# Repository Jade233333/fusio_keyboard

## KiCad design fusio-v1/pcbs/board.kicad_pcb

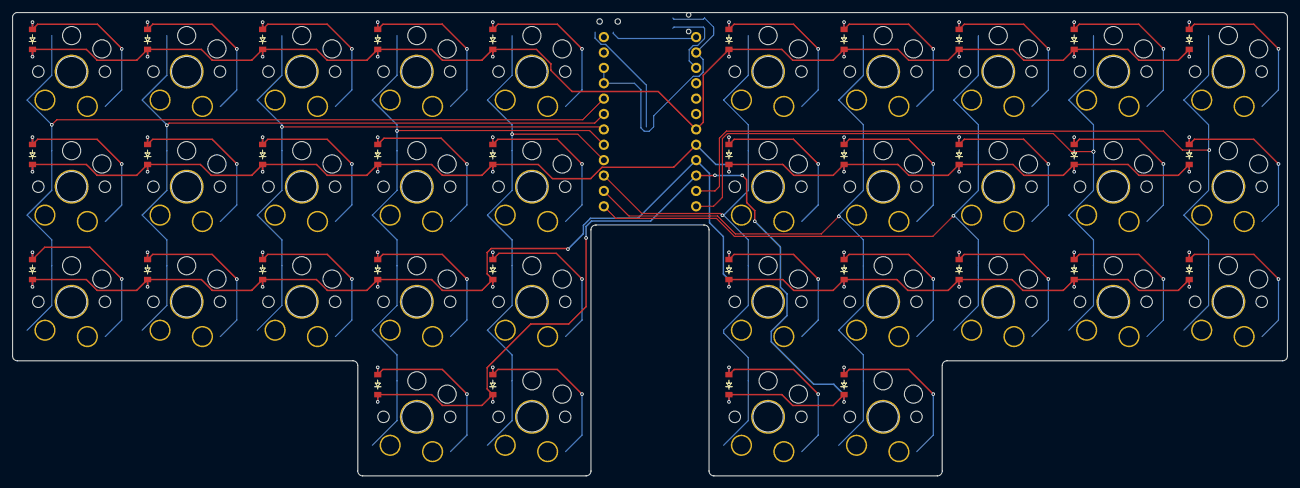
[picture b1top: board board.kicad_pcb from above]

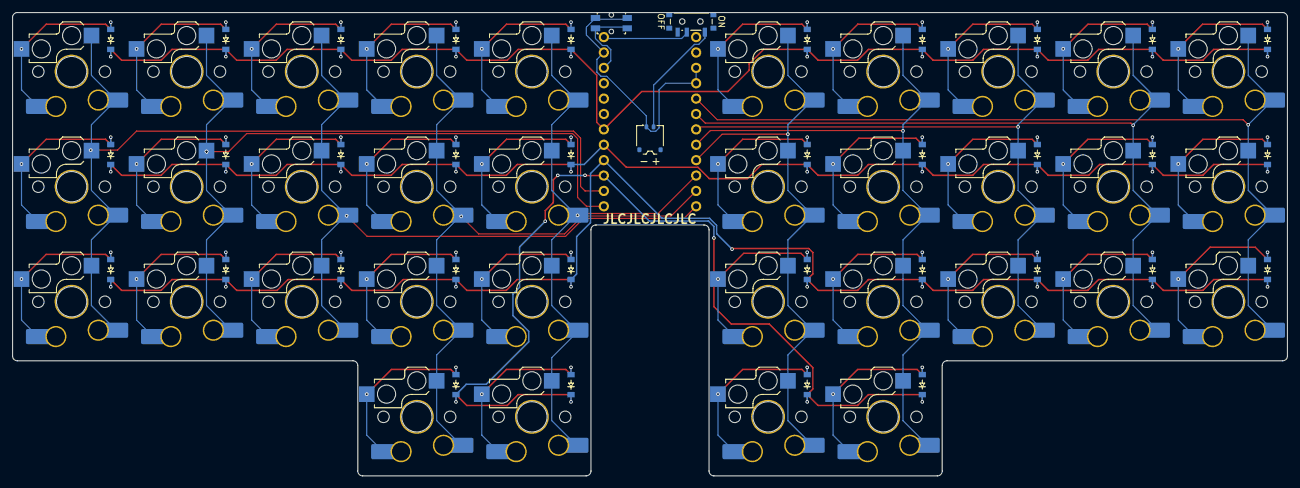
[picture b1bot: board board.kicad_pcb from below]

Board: 2 copper layers, 210.5 x 76.5 mm, 106 parts (71 on the bottom side), 52 nets.

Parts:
CONN1: battery_connector_molex_pico_ezmate_1x02
D1, D2, D3, D4, D5, D6, D7, D8, D9, D10, D11, D12, D13, D14, D15, D16, D17, D18, D19, D20, D21, D22, D23, D24, D25, D26, D27, D28, D29, D30, D31, D32, D33, D34: diode_tht_sod123
MCU1: mcu_supermini_nrf52840
PWR1: power_switch_smd_side
RST1: reset_switch_smd_side
S1, S2, S3, S4, S5, S6, S7, S8, S9, S10, S11, S12, S13, S14, S15, S16, S17, S18, S19, S20, S21, S22, S23, S24, S25, S26, S27, S28, S29, S30, S31, S32, S33, S34: switch_gateron_ks27_ks33
S35, S36, S37, S38, S39, S40, S41, S42, S43, S44, S45, S46, S47, S48, S49, S50, S51, S52, S53, S54, S55, S56, S57, S58, S59, S60, S61, S62, S63, S64, S65, S66, S67, S68: switch_choc_v1_v2

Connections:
BAT_P: CONN1.2, PWR1.1
GND: CONN1.1, MCU1.2, MCU1.21, MCU1.22, RST1.1, RST1.3
P2: MCU1.20, S1.1, S2.1, S3.1, S35.1, S36.1, S37.1
P3: MCU1.19, S4.1, S5.1, S6.1, S38.1, S39.1, S40.1
P4: MCU1.18, S7.1, S8.1, S9.1, S41.1, S42.1, S43.1
P5: MCU1.17, S10.1, S11.1, S12.1, S13.1, S44.1, S45.1, S46.1, S47.1
P6: MCU1.16, S14.1, S15.1, S16.1, S17.1, S48.1, S49.1, S50.1, S51.1
P7: MCU1.15, S18.1, S19.1, S20.1, S21.1, S52.1, S53.1, S54.1, S55.1
P8: MCU1.14, S22.1, S23.1, S24.1, S25.1, S56.1, S57.1, S58.1, S59.1
P9: MCU1.13, S26.1, S27.1, S28.1, S60.1, S61.1, S62.1
P10: MCU1.12, S29.1, S30.1, S31.1, S63.1, S64.1, S65.1
P14: D10.1, D14.1, D18.1, D22.1, MCU1.10
P15: D1.1, D4.1, D7.1, D11.1, D15.1, D19.1, D23.1, D26.1, D29.1, D32.1, MCU1.9
P16: MCU1.11, S32.1, S33.1, S34.1, S66.1, S67.1, S68.1
P18: D2.1, D5.1, D8.1, D12.1, D16.1, D20.1, D24.1, D27.1, D30.1, D33.1, MCU1.8
P19: D3.1, D6.1, D9.1, D13.1, D17.1, D21.1, D25.1, D28.1, D31.1, D34.1, MCU1.7
RAW: MCU1.1, PWR1.2
RST: MCU1.3, RST1.2, RST1.4
leftindex_bottom: D11.2, S11.2, S45.2
leftindex_home: D12.2, S12.2, S46.2
leftindex_thumb: D10.2, S10.2, S44.2
leftindex_top: D13.2, S13.2, S47.2
leftinner_bottom: D15.2, S15.2, S49.2
leftinner_home: D16.2, S16.2, S50.2
leftinner_thumb: D14.2, S14.2, S48.2
leftinner_top: D17.2, S17.2, S51.2
leftmiddle_bottom: D7.2, S7.2, S41.2
leftmiddle_home: D8.2, S8.2, S42.2
leftmiddle_top: D9.2, S9.2, S43.2
leftpinky_bottom: D1.2, S1.2, S35.2
leftpinky_home: D2.2, S2.2, S36.2
leftpinky_top: D3.2, S3.2, S37.2
leftring_bottom: D4.2, S4.2, S38.2
leftring_home: D5.2, S5.2, S39.2
leftring_top: D6.2, S6.2, S40.2
rightindex_bottom: D23.2, S23.2, S57.2
rightindex_home: D24.2, S24.2, S58.2
rightindex_thumb: D22.2, S22.2, S56.2
rightindex_top: D25.2, S25.2, S59.2
rightinner_bottom: D19.2, S19.2, S53.2
rightinner_home: D20.2, S20.2, S54.2
rightinner_thumb: D18.2, S18.2, S52.2
rightinner_top: D21.2, S21.2, S55.2
rightmiddle_bottom: D26.2, S26.2, S60.2
rightmiddle_home: D27.2, S27.2, S61.2
rightmiddle_top: D28.2, S28.2, S62.2
rightpinky_bottom: D32.2, S32.2, S66.2
rightpinky_home: D33.2, S33.2, S67.2
rightpinky_top: D34.2, S34.2, S68.2
rightring_bottom: D29.2, S29.2, S63.2
rightring_home: D30.2, S30.2, S64.2
rightring_top: D31.2, S31.2, S65.2

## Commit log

2025-04-29 first draft
2025-04-29 add .gitignore
2025-04-29 plate
2025-04-29 add submodule footprint database
2025-04-29 component position confirm
2025-04-30 pcb, plate shape commited:
2025-05-03 case design down waiting for routing
2025-05-03 tolerance edite
2025-05-03 pcb done
2025-05-03 add jlc silkscreen
2025-05-04 support gateron
2025-05-04 add jlc
2025-05-05 via size correction
2025-09-02 test for name
